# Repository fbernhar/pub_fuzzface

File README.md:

```text

      ███████╗██╗   ██╗███████╗███████╗
      ██╔════╝██║   ██║╚══███╔╝╚══███╔╝
      █████╗  ██║   ██║  ███╔╝   ███╔╝ 
      ██╔══╝  ██║   ██║ ███╔╝   ███╔╝  
      ██║     ╚██████╔╝███████╗███████╗
      ╚═╝      ╚═════╝ ╚══════╝╚══════╝
      
        ███████╗ █████╗  ██████╗███████╗
        ██╔════╝██╔══██╗██╔════╝██╔════╝
        █████╗  ███████║██║     █████╗  
        ██╔══╝  ██╔══██║██║     ██╔══╝  
        ██║     ██║  ██║╚██████╗███████╗
        ╚═╝     ╚═╝  ╚═╝ ╚═════╝╚══════╝

%%%%%%%%%%%%%%%
% Description %
%%%%%%%%%%%%%%%

A raw, unapologetic guide to face the fuzz

fuzz-face/
├── kicad/     # PCB + schematic files + simulations
├── ltspice/   # schematic files + circuit simulations
├── dsp/       # signal processing libary + algorithms
└── README.md  # project overview 

%%%%%%%%%%%%
% Software %
%%%%%%%%%%%%

LTspice
https://www.analog.com/en/resources/design-tools-and-calculators/ltspice-simulator.html

LiveSpice
https://www.livespice.org/

KiCad
https://www.kicad.org/

%%%%%%%%%%%%%%
% Literature %
%%%%%%%%%%%%%%

Analysis (Fuzz Face Circuit)
- https://www.electrosmash.com/fuzz-face
- http://geofex.com/article_folders/fuzzface/fftech.htm

KiCad (Fuzz Face Build)
- https://forum.kicad.info/t/fuzz-face-tone-bender-projects-updated-05-22-23/41450
- https://barbarach.com/building-a-fuzz-face-clone-intro-analysis/

KiCad (Supporting wav files)
https://forum.kicad.info/t/experimental-setup-for-kicad-ngspice-supporting-wav-audio-files/52875

LTSpice (Fuzz Face Build)
- https://z2dsp.com/2017/09/04/modelling-fuzz/

Wave-Digital-Filter (Fuzz Face UniversityProject)
- https://ccrma.stanford.edu/wiki/Wave_Digital_Filters_applied_to_the_Dunlop_%22Fuzz_Face%22_Distortion_Circuit

%%%%%%%%%%%%%%
% Disclaimer %
%%%%%%%%%%%%%%

This project is provided for educational purposes only. The circuit, PCB files,
simulation setup, and documentation are not guaranteed to be correct, safe,
or suitable for production.

Before ordering PCBs or building hardware, double-check all footprints,
pinouts, capacitor polarity, power connections, ERC/DRC results, and Gerber files.

Use at your own risk.

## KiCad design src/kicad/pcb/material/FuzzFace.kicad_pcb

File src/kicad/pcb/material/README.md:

## Note

The `AC128.MOD` file was taken from a post by KiCad forum user **invntefx**:

https://forum.kicad.info/t/fuzz-face-tone-bender-projects-updated-05-22-23/41450

Please note that this file may be subject to its original author’s license or usage terms.

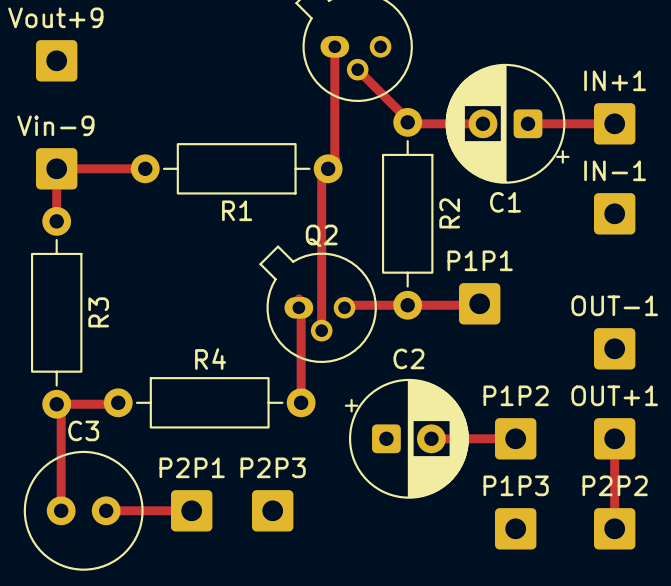
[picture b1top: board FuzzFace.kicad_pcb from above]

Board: 2 copper layers, 21 parts (0 on the bottom side), 11 nets.

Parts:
C1: 2.2uF; CP_Radial_D6.3mm_P2.50mm
C2: 20uF; CP_Radial_D6.3mm_P2.50mm
C3: 0.01uF; C_Radial_D6.3mm_H5.0mm_P2.50mm
IN+1: SolderWire-0.5sqmm_1x01_D0.9mm_OD2.3mm
IN-1: SolderWire-0.5sqmm_1x01_D0.9mm_OD2.3mm
OUT+1: SolderWire-0.5sqmm_1x01_D0.9mm_OD2.3mm
OUT-1: SolderWire-0.5sqmm_1x01_D0.9mm_OD2.3mm
P1P1, P1P2, P1P3, P2P1, P2P2, P2P3: SolderWire-0.5sqmm_1x01_D0.9mm_OD2.3mm
Q1, Q2: AC128; TO-18-3
R1: 33K; R_Axial_DIN0207_L6.3mm_D2.5mm_P10.16mm_Horizontal
R2: 100K; R_Axial_DIN0207_L6.3mm_D2.5mm_P10.16mm_Horizontal
R3: 470; R_Axial_DIN0207_L6.3mm_D2.5mm_P10.16mm_Horizontal
R4: 8.2K; R_Axial_DIN0207_L6.3mm_D2.5mm_P10.16mm_Horizontal
Vin-9: -9V; SolderWire-0.5sqmm_1x01_D0.9mm_OD2.3mm
Vout+9: +9V; SolderWire-0.5sqmm_1x01_D0.9mm_OD2.3mm

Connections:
GND: C2.1, IN-1.1 (Pin_1_1), OUT-1.1 (Pin_1_1), P1P3.1 (Pin_1_1), P2P3.1 (Pin_1_1), Q1.3 (E), Vout+9.1 (Pin_1_1)
unnamed: C3.1, R3.2, R4.1
unnamed: C1.1, IN+1.1 (Pin_1_1)
unnamed: OUT+1.1 (Pin_1_1), P2P2.1 (Pin_1_1)
unnamed: P1P1.1 (Pin_1_1), Q2.3 (E), R2.2
unnamed: C2.2, P1P2.1 (Pin_1_1)
unnamed: C3.2, P2P1.1 (Pin_1_1)
unnamed: C1.2, Q1.2 (B), R2.1
unnamed: Q1.1 (C), Q2.2 (B), R1.1
unnamed: Q2.1 (C), R4.2
unnamed: R1.2, R3.1, Vin-9.1 (Pin_1_1)

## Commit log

2026-05-13 inital commit
2026-06-20 updated readme and mod file
